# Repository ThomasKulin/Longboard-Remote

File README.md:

# Longboard-Remote
A handheld Bluetooth remote for the electric longboard

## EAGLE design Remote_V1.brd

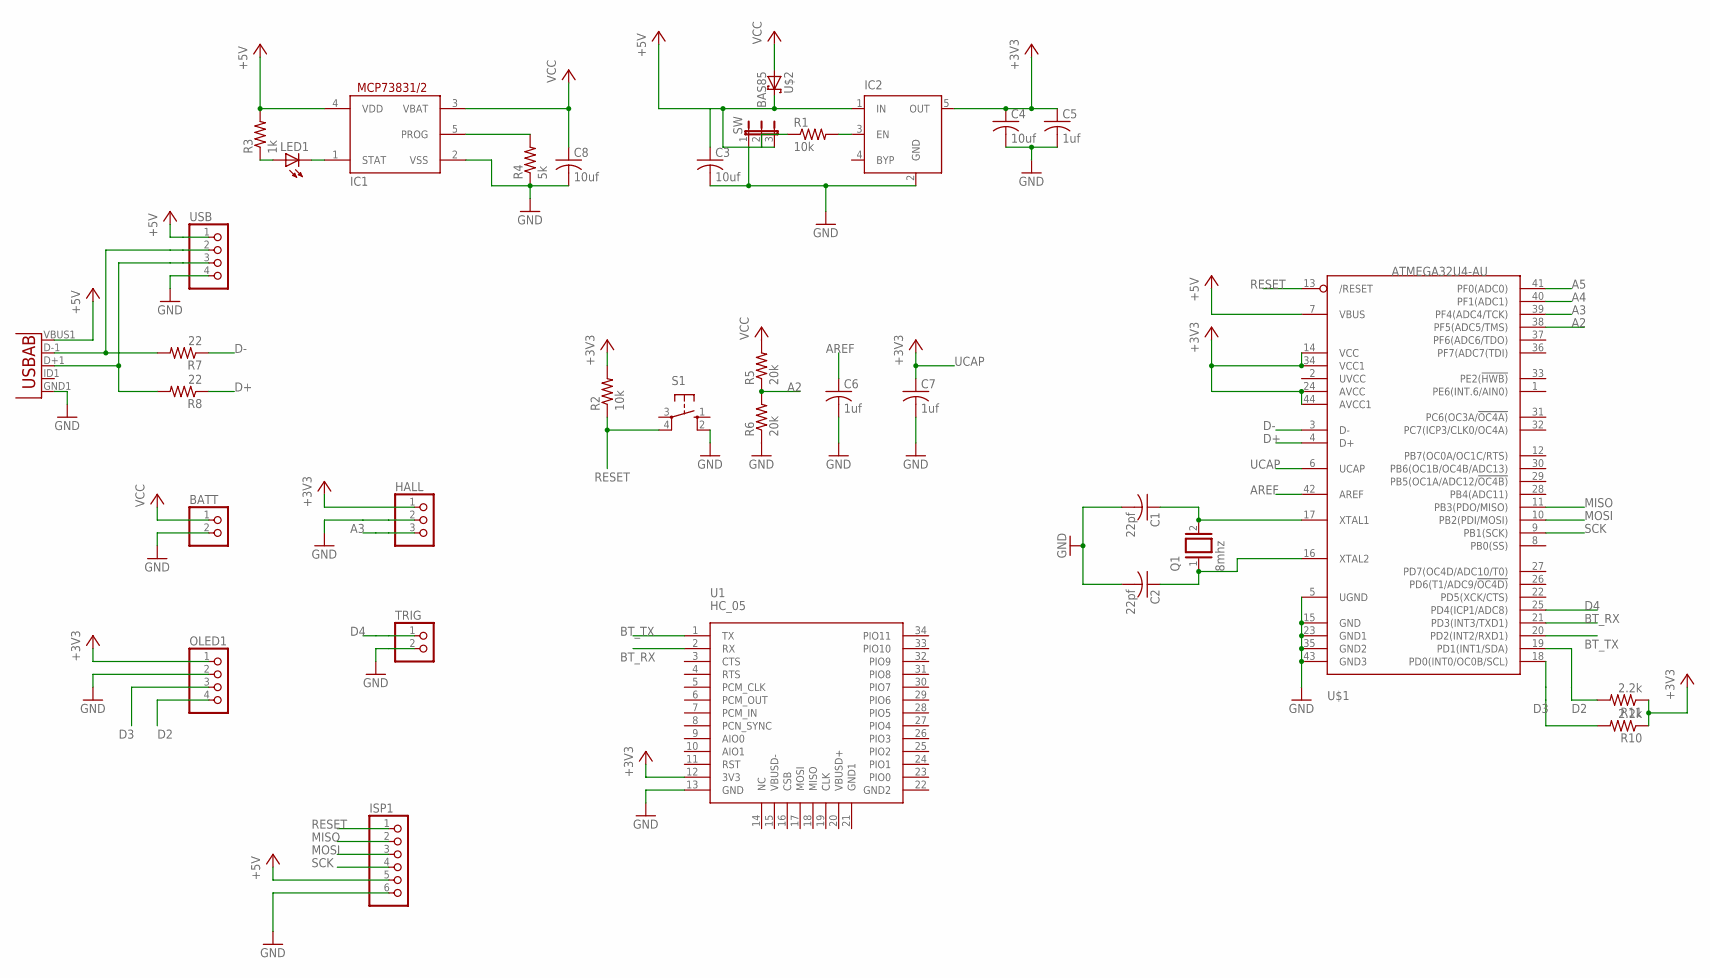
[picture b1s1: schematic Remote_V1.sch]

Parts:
BATT: PINHD-1X2; 1X02
C1, C2: 22pf; C025-030X050
C3, C4, C8: 10uf; C0603
C5, C6, C7: 1uf; C0603
HALL: PINHD-1X3; 1X03
IC1: MCP73831/OT; SOT23-5L
IC2: MIC5219XX; SOT23-5
ISP1: PINHD-1X6; 1X06
LED1: LEDCHIPLED_0805; CHIPLED_0805
OLED1: PINHD-1X4; 1X04
Q1: 8mhz; QS
R1, R2: 10k; R0603
R3: 1k; R0603
R4: 5k; R0603
R5, R6: 20k; R0603
R7, R8: 22; R0603
R10, R11: 2.2k; R0603
S1: 10-XX; B3F-10XX
SW: JP2E; JP2
TRIG: PINHD-1X2; 1X02
U1: HC_05; BLUETOOTH_SMD
U2: USB""; USB-MICRO-SMD
U$1: ATMEGA32U4-AU; TQFP44
U$2: BAS85; SOD80C
USB: PINHD-1X4; 1X04

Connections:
+3V3: C4.1, C5.1, HALL.1, IC2.5 (OUT), OLED1.1, R2.2, R10.1, R11.1, U1.12 (3V3), U$1.14 (VCC), U$1.24 (AVCC), U$1.34 (VCC1), U$1.44 (AVCC1)
+5V: C3.1, IC1.4 (VDD), IC2.1 (IN), ISP1.5, R3.2, SW.3, U2.VBUS1 (VBUS), U$1.7 (VBUS), U$2.1 (K), USB.1
A2: R5.1, R6.2, U$1.38 (PF5(ADC5/TMS))
A3: HALL.3, U$1.39 (PF4(ADC4/TCK))
A4: U$1.40 (PF1(ADC1))
A5: U$1.41 (PF0(ADC0))
AREF: C6.1, U$1.42 (AREF)
BT_RX: U1.2 (RX), U$1.21 (PD3(INT3/TXD1))
BT_TX: U1.1 (TX), U$1.20 (PD2(INT2/RXD1))
D2: OLED1.4, R11.2, U$1.19 (PD1(INT1/SDA))
D3: OLED1.3, R10.2, U$1.18 (PD0(INT0/OC0B/SCL))
D4: TRIG.1, U$1.25 (PD4(ICP1/ADC8))
D+: R8.1, U$1.4 (D+)
D-: R7.1, U$1.3 (D-)
GND: BATT.2, C1.2, C2.2, C3.2, C4.2, C5.2, C6.2, C7.2, C8.2, HALL.2, IC1.2 (VSS), IC2.2 (GND), ISP1.6, OLED1.2, R4.1, R6.1, S1.2 (S1), SW.1, TRIG.2, U1.13 (GND), U2.GND1 (GND), U$1.5 (UGND), U$1.15 (GND), U$1.23 (GND1), U$1.35 (GND2), U$1.43 (GND3), USB.4
MISO: ISP1.2, U$1.11 (PB3(PDO/MISO))
MOSI: ISP1.3, U$1.10 (PB2(PDI/MOSI))
unnamed: C1.1, Q1.2, U$1.17 (XTAL1)
unnamed: C2.1, Q1.1, U$1.16 (XTAL2)
unnamed: R1.1, SW.2
unnamed: IC2.3 (EN), R1.2
unnamed: LED1.A, R3.1
unnamed: IC1.1 (STAT), LED1.C
unnamed: IC1.5 (PROG), R4.2
unnamed: R7.2, U2.D-1 (D-), USB.2
unnamed: R8.2, U2.D+1 (D+), USB.3
RESET: ISP1.1, R2.1, S1.4 (P1), U$1.13 (/RESET)
SCK: ISP1.4, U$1.9 (PB1(SCK))
UCAP: C7.1, U$1.6 (UCAP)
VCC: BATT.1, C8.1, IC1.3 (VBAT), R5.2, U$2.2 (A)

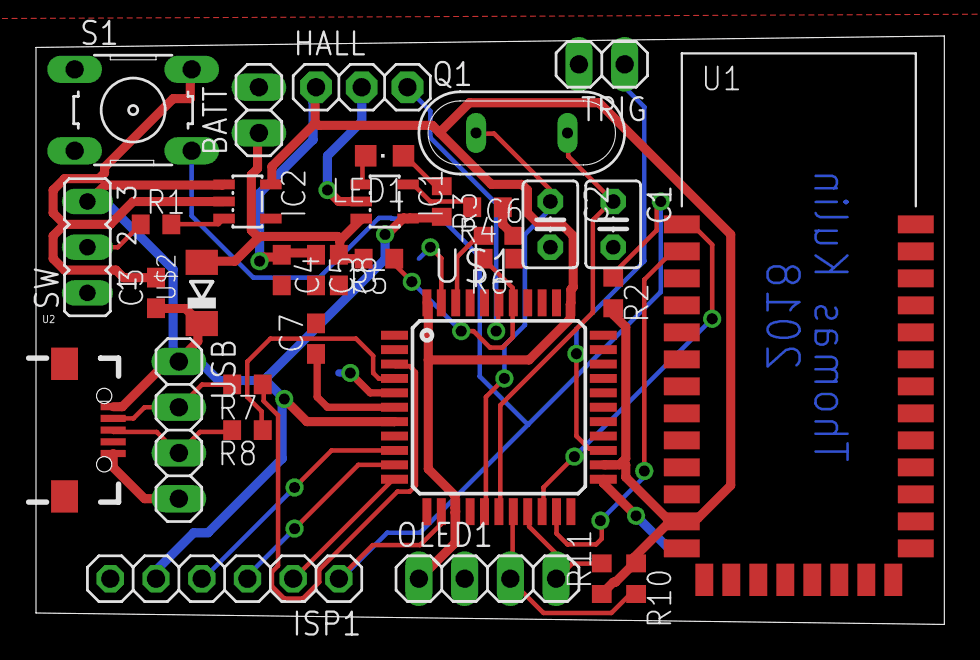
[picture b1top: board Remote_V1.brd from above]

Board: 2 copper layers, 50.5 x 32.7 mm, 34 parts (0 on the bottom side), 28 nets.

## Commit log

2019-11-06 circuit for handheld remote
